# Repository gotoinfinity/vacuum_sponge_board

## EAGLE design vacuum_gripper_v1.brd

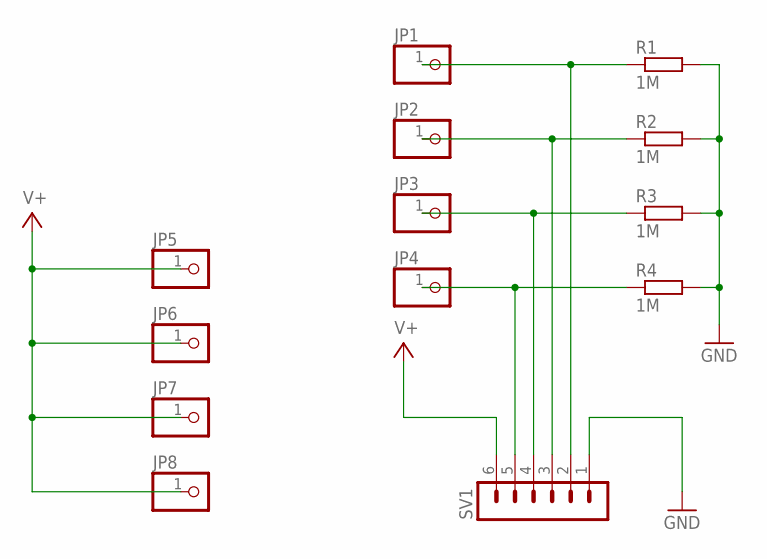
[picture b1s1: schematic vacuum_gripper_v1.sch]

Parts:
JP1, JP2, JP3, JP4, JP5, JP6, JP7, JP8: PINHD-1X1; 1X01
R1, R2, R3, R4: 1M; R1206
SV1: MA06-1

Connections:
GND: R1.2, R2.2, R3.2, R4.2, SV1.1
unnamed: JP1.1, R1.1, SV1.2
unnamed: JP2.1, R2.1, SV1.3
unnamed: JP3.1, R3.1, SV1.4
unnamed: JP4.1, R4.1, SV1.5
V+: JP5.1, JP6.1, JP7.1, JP8.1, SV1.6

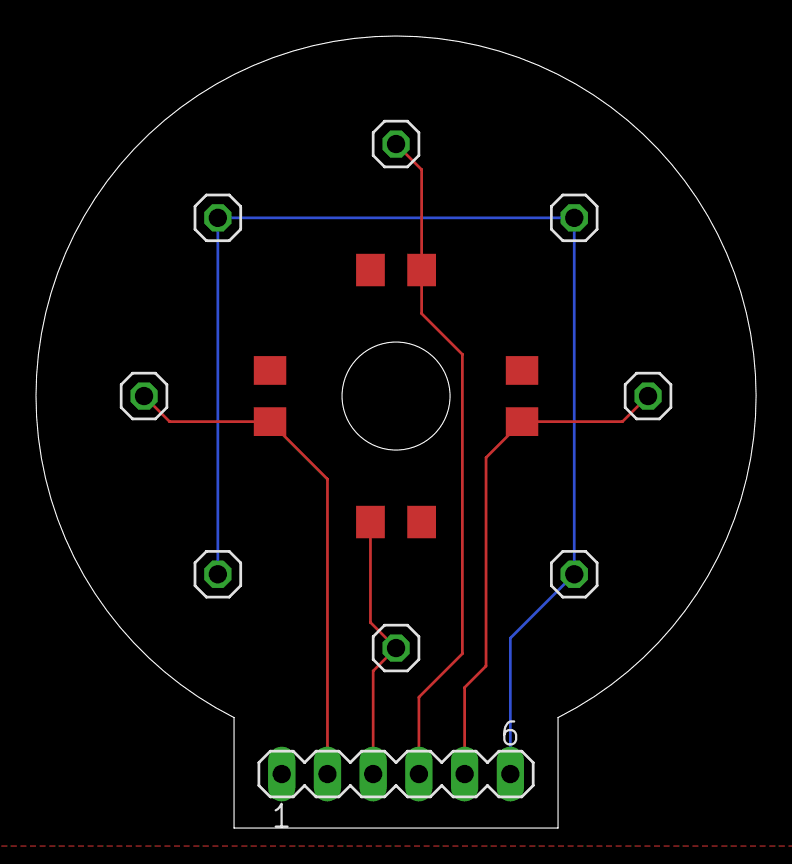
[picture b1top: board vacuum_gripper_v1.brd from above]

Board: 2 copper layers, 40.0 x 44.0 mm, 13 parts (0 on the bottom side), 6 nets.

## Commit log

2022-05-13 upload files
